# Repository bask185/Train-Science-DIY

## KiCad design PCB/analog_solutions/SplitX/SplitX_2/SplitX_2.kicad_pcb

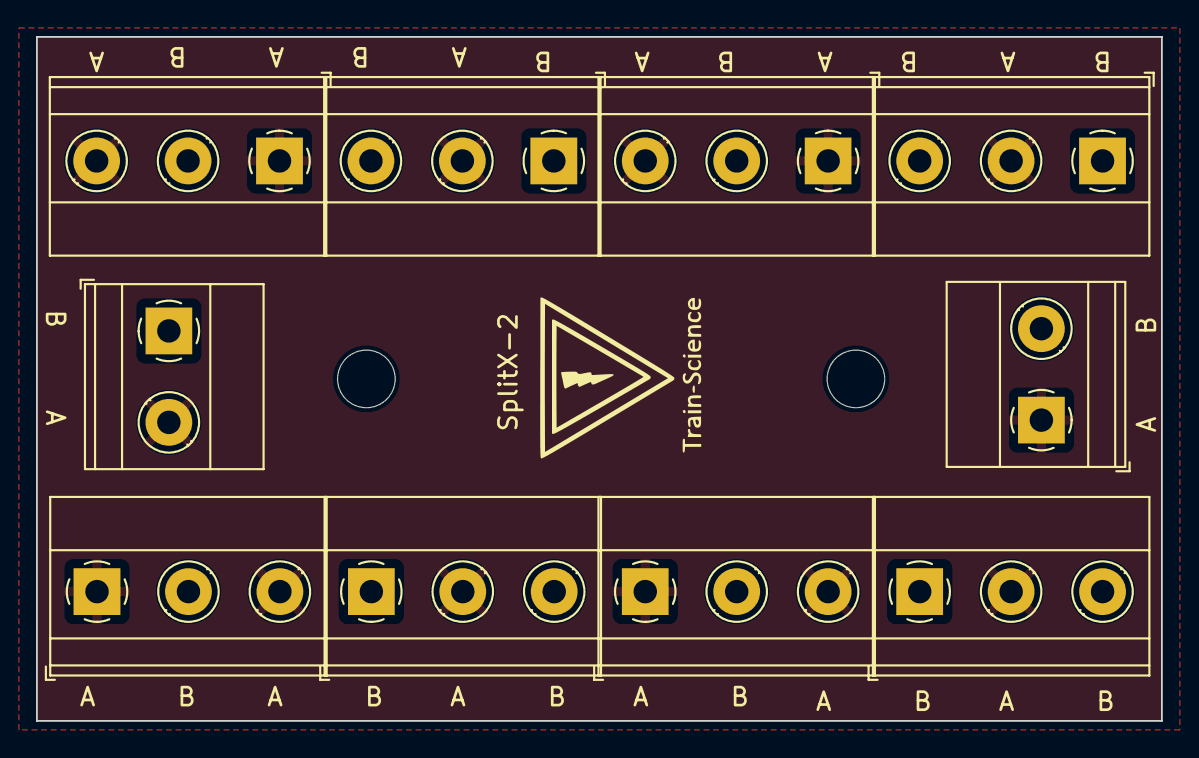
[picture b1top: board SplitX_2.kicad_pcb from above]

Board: 2 copper layers, 62.5 x 38.0 mm, 10 parts (0 on the bottom side), 2 nets, no tracks yet.

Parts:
J1, J10: Screw_Terminal_01x02; TerminalBlock_Phoenix_MKDS-1,5-2-5.08_1x02_P5.08mm_Horizont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
J2, J3, J4, J5, J7, J8, J9: Screw_Terminal_01x03; TerminalBlock_Phoenix_MKDS-1,5-3-5.08_1x03_P5.08mm_Horizont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
Je: Screw_Terminal_01x03; TerminalBlock_Phoenix_MKDS-1,5-3-5.08_1x03_P5.08mm_Horizont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

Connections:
A: J1.2, J2.2, J3.1, J3.3, J4.1, J4.3, J5.2, J7.1, J7.3, J8.1, J8.3, J9.2, J10.1, Je.2
B: J1.1, J2.1, J2.3, J3.2, J4.2, J5.1, J5.3, J7.2, J8.2, J9.1, J9.3, J10.2, Je.1, Je.3

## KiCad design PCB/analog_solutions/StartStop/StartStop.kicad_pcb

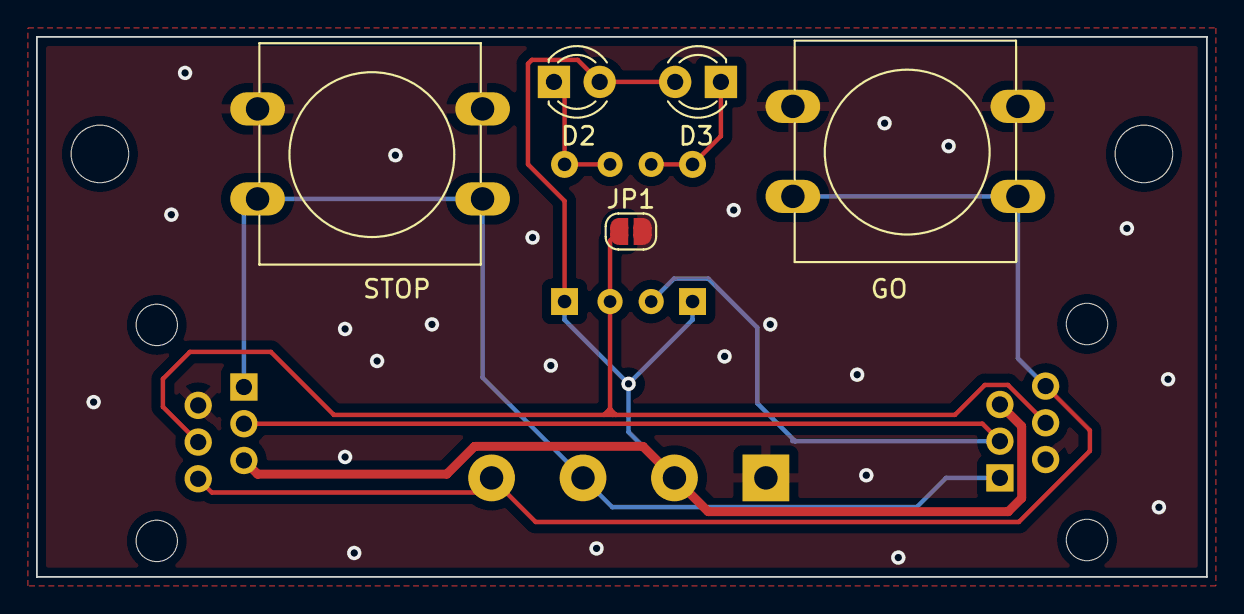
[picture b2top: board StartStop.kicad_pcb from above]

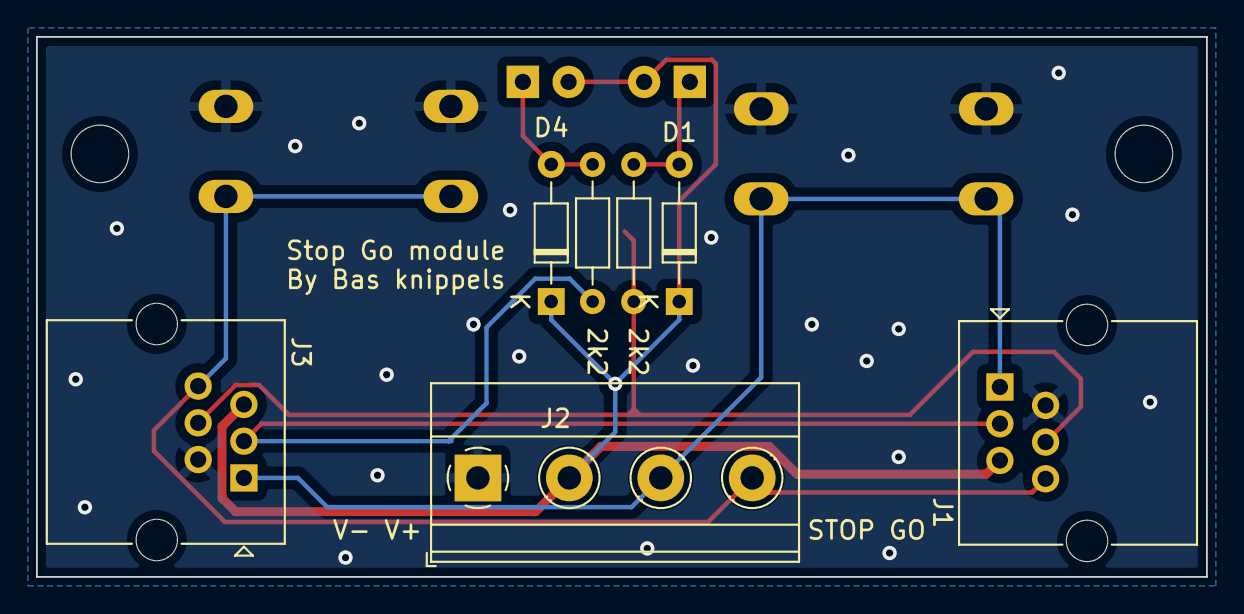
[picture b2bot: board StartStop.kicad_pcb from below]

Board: 2 copper layers, 65.0 x 30.0 mm, 12 parts (7 on the bottom side), 8 nets.

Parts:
D1, D4: D; D_DO-34_SOD68_P7.62mm_Horizontal
D2, D3: LED; LED_D3.0mm
GO: SW_SPST; SW_PUSH-12mm
J1, J3: RJ12; RJ25_Wayconn_MJEA-660X1_Horizontal
J2: Screw_Terminal_01x04; TerminalBlock_Phoenix_MKDS-1,5-4-5.08_1x04_P5.08mm_Horizont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
JP1: SolderJumper_2_Open; SolderJumper-2_P1.3mm_Open_RoundedPad1.0x1.5mm
R1, R2: 2k2; R_Axial_DIN0204_L3.6mm_D1.6mm_P7.62mm_Horizontal
STOP: SW_SPST; SW_PUSH-12mm

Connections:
/GO: GO.2 (B), J1.6, J2.4, J3.6
/GO_LED: J1.4, J3.4, JP1.1 (A), R1.1
/STOP: J1.1, J2.3, J3.1, STOP.2 (B)
/STOP_LED: J1.3, J3.3, R2.1
GND: GO.1 (A), J1.2, J2.1, J3.2, JP1.2 (B), STOP.1 (A)
unnamed: D1.2 (A), D2.1 (K), R1.2
unnamed: D3.1 (K), D4.2 (A), R2.2
VCC: D1.1 (K), D2.2 (A), D3.2 (A), D4.1 (K), J1.5, J2.2, J3.5

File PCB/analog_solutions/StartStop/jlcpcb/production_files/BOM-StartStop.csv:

Comment,Designator,Footprint,LCSC
SolderJumper_2_Open,JP1,SolderJumper-2_P1.3mm_Open_RoundedPad1.0x1.5mm,
LED,D3,LED_D3.0mm,
LED,D2,LED_D3.0mm,
Screw_Terminal_01x04,J2,"TerminalBlock_Phoenix_MKDS-1,5-4-5.08_1x04_P5.08mm_Horizontal",
2k2,R2,R_Axial_DIN0204_L3.6mm_D1.6mm_P7.62mm_Horizontal,
D,D1,D_DO-34_SOD68_P7.62mm_Horizontal,
2k2,R1,R_Axial_DIN0204_L3.6mm_D1.6mm_P7.62mm_Horizontal,
D,D4,D_DO-34_SOD68_P7.62mm_Horizontal,
RJ12,J3,RJ25_Wayconn_MJEA-660X1_Horizontal,
RJ12,J1,RJ25_Wayconn_MJEA-660X1_Horizontal,

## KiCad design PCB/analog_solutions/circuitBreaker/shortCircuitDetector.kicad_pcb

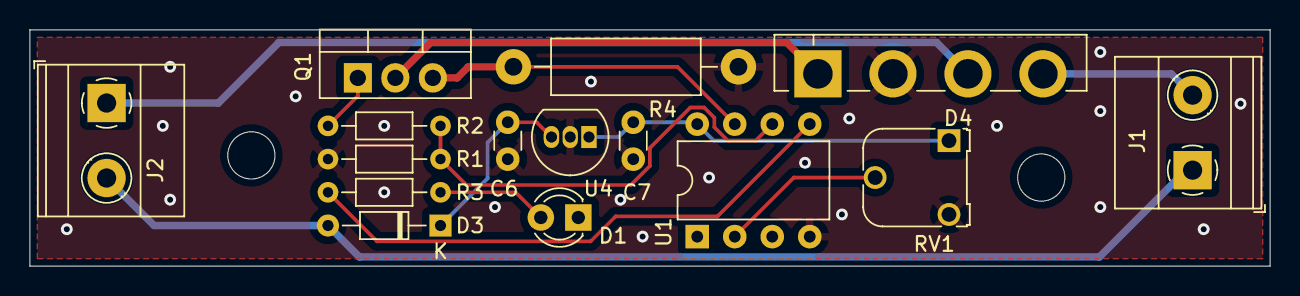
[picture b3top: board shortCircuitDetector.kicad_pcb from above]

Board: 2 copper layers, 84.0 x 16.0 mm, 15 parts (0 on the bottom side), 13 nets.

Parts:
C6: 330nF; C_Disc_D3.0mm_W1.6mm_P2.50mm
C7: 100nF; C_Disc_D3.0mm_W1.6mm_P2.50mm
D1: LED; LED_D3.0mm
D3: D; D_DO-34_SOD68_P7.62mm_Horizontal
D4: D; Diode_Bridge_Vishay_GBL
J1: AC IN; TerminalBlock_Phoenix_MKDS-1,5-2-5.08_1x02_P5.08mm_Horizont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
J2: AC_OUT; TerminalBlock_Phoenix_MKDS-1,5-2-5.08_1x02_P5.08mm_Horizont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
Q1: IRF540N; TO-220-3_Vertical
R1: 10k; R_Axial_DIN0204_L3.6mm_D1.6mm_P7.62mm_Horizontal
R2: 22R; R_Axial_DIN0204_L3.6mm_D1.6mm_P7.62mm_Horizontal
R3: R; R_Axial_DIN0204_L3.6mm_D1.6mm_P7.62mm_Horizontal
R4: 1R; R_Axial_DIN0411_L9.9mm_D3.6mm_P15.24mm_Horizontal
RV1: R_Potentiometer; Potentiometer_Runtron_RM-065_Vertical
U1: ATtiny45-20P; DIP-8_W7.62mm
U4: L78L05_TO92; TO-92_Inline

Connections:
+5V: C7.1, RV1.1, U1.8 (VCC), U4.1 (VO)
/adjust: RV1.2, U1.2 (XTAL1/PB3)
/currSens: Q1.3 (S), R4.1, U1.7 (PB2)
/led: R3.1, U1.5 (AREF/PB0)
/on_off: R1.2, R2.1, U1.6 (PB1)
GND: C6.2, C7.2, D1.1 (K), D4.2 (-), R1.1, R4.2, RV1.3, U1.4 (GND), U4.2 (GND)
unnamed: D1.2 (A), R3.2
unnamed: D3.2 (A), J1.1, J2.2
unnamed: D4.1 (+), Q1.2 (D)
unnamed: D4.3, J2.1
unnamed: D4.4, J1.2
unnamed: Q1.1 (G), R2.2
VCC: C6.1, D3.1 (K), U4.3 (VI)

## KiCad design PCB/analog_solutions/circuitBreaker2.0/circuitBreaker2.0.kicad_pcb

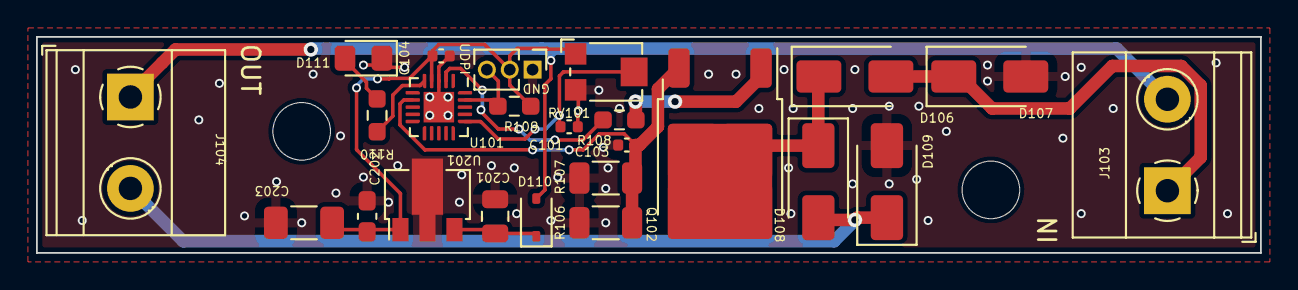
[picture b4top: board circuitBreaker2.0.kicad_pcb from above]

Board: 2 copper layers, 68.0 x 12.0 mm, 24 parts (0 on the bottom side), 14 nets.

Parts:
C101, C103, C104: 100nF; C_0402_1005Metric
C201: 470nF; C_0805_2012Metric
C202: 100nF; C_0603_1608Metric_Pad1.08x0.95mm_HandSolder
C203: 100uF; C_1206_3216Metric_Pad1.33x1.80mm_HandSolder
D106, D107, D108, D109: D; D_SMA
D110: 1N4148WS; D_SOD-323
D111: LED; LED_0805_2012Metric_Pad1.15x1.40mm_HandSolder
J103, J104: Screw_Terminal_01x02; TerminalBlock_Phoenix_MKDS-1,5-2-5.08_1x02_P5.08mm_Horizont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
J105: Conn_01x03; PinHeader_1x03_P1.27mm_Vertical
Q102: 4A_DARLINGTON; TO-252-2
R106, R107: 0R1; R_1206_3216Metric
R108, R109: 10k; R_0603_smalltext
R110: 470R; R_0603_smalltext
RV101: R_Potentiometer; Potentiometer_Bourns_TC33X_Vertical
U101: ATtiny1616-M; VQFN-20-1EP_3x3mm_P0.4mm_EP1.7x1.7mm
U201: L78L05_SOT89; SOT-89-3

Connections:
+5V: C104.1, C202.1, C203.1, J105.2, R109.1, RV101.1, U101.4 (VCC), U201.1 (OUT)
/CS: C103.1, Q102.3 (E), R106.1, R107.2, U101.7 (PA6)
/LED: R110.2, U101.5 (PA4)
/ON/OFF: R108.2, U101.2 (PA3)
/UDPI: J105.3, R109.2, U101.19 (~RESET/PA0)
/power control: C101.1, RV101.2, U101.16 (PC1)
GND: C101.2, C103.2, C104.2, C201.2, C202.2, C203.2, D107.2 (A), D109.2 (A), D111.1 (K), J105.1, R106.2, R107.1, RV101.3, U101.3 (GND), U101.21 (GND), U201.2 (GND)
unnamed: D106.2 (A), D107.1 (K), J103.1
unnamed: D106.1 (K), D108.1 (K), Q102.2 (C)
unnamed: D108.2 (A), D109.1 (K), J104.2
unnamed: D110.2 (A), J103.2, J104.1
unnamed: D111.2 (A), R110.1
unnamed: Q102.1 (B), R108.1
VCC: C201.1, D110.1 (K), U201.3 (IN)

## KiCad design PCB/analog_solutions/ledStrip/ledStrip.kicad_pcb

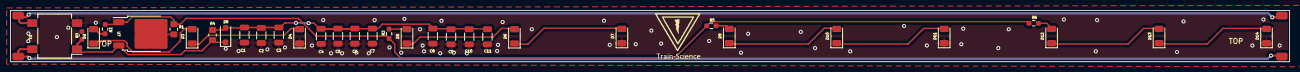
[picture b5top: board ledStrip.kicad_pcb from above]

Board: 2 copper layers, 250.0 x 10.0 mm, 37 parts (0 on the bottom side), 19 nets.

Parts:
C1, C2, C3, C4, C5, C6, C7, C8, C9, C10, C11: 22uF; C_1206_3216Metric
D1: D_Bridge_+-AA; Diode_Bridge_Diotec_SO-DIL-Slim
D2, D3, D4, D5, D6, D7, D9, D10, D11, D12, D13, D14: LED; LED_1206_3216Metric
D8: SM4007; D_SOD-123F
J1, J2, J3, J4: Conn_01x01_Pin; 01_solderpad_2.54
R1: 220R; R_0805_handsolder-smalltext
R2, R3, R5, R6: 10R; R_0603_smalltext
R4: 100R; R_0805_handsolder-smalltext
U7: LM317_TO-252; TO-252-2
U8: 100nF; C_0603_1608Metric

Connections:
/Vled: R1.2, R2.1, R3.1, R5.1, R6.1, U7.1 (ADJ)
AC1: D1.4, J1.1, J3.1
AC2: D1.3, J2.1, J4.1
GND: C1.2, C2.2, C3.2, C4.2, C5.2, C6.2, C7.2, C8.2, C9.2, C10.2, C11.2, D1.2 (-), D4.1 (K), D7.1 (K), D11.1 (K), D14.1 (K), U8.2
unnamed: D2.2 (A), R2.2
unnamed: D2.1 (K), D3.2 (A)
unnamed: D3.1 (K), D4.2 (A)
unnamed: D5.2 (A), R3.2
unnamed: D5.1 (K), D6.2 (A)
unnamed: D6.1 (K), D7.2 (A)
unnamed: C1.1, C2.1, C3.1, C4.1, C5.1, C6.1, C7.1, C8.1, C9.1, C10.1, C11.1, D8.2 (A), R4.1
unnamed: D9.2 (A), R5.2
unnamed: D9.1 (K), D10.2 (A)
unnamed: D10.1 (K), D11.2 (A)
unnamed: D12.2 (A), R6.2
unnamed: D12.1 (K), D13.2 (A)
unnamed: D13.1 (K), D14.2 (A)
unnamed: R1.1, U7.2 (VO)
VCC: D1.1 (+), D8.1 (K), R4.2, U7.3 (VI), U8.1

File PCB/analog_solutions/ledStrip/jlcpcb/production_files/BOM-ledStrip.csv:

Comment,Designator,Footprint,LCSC
100nF,U8,C_0603_1608Metric,C14663
100R,R4,R_0805_handsolder-smalltext,C17408
220R,R1,R_0805_handsolder-smalltext,C17557
LED,"D10,D11,D12,D13,D14,D2,D3,D4,D5,D6,D7,D9",LED_1206_3216Metric,C219232
10R,"R2,R3,R5,R6",R_0603_smalltext,C22859
D_Bridge_+-AA,D1,Diode_Bridge_Diotec_SO-DIL-Slim,C5377
SM4007,D8,D_SOD-123F,C64898
LM317_TO-252,U7,TO-252-2,C75510
22uF,C1,C_1206_3216Metric,C96123
